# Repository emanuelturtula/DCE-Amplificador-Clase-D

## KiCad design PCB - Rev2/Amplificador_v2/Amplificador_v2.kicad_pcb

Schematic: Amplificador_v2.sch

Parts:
C1, C3, C4, C5, C10, C11, C17, C19, C26, C34: 100n; C_0805_2012Metric
C2, C9, C12, C13, C55, C62, C65, C72, C74: 10u; CP_Elec_4x5.3
C6, C25: 220n; C_0805_2012Metric
C7, C14, C15: 3.3n; C_0805_2012Metric
C8, C22, C45, C46, C48, C49, C52: 1u; C_0805_2012Metric
C16: 1u; CP_Radial_D5.0mm_P2.00mm
C18: 33p; C_0805_2012Metric
C20, C33, C64, C73: 10u; CP_Radial_D4.0mm_P1.50mm
C21, C43, C44: 100u; CP_Radial_D8.0mm_P3.50mm
C23, C24: 10u; C_0805_2012Metric
C27, C28: 1n; C_0805_2012Metric
C29, C30, C32: C; C_1206_3216Metric
C31: 330n; C_Rect_L18.0mm_W5.0mm_P15.00mm_FKS3_FKP3
C35, C36, C37, C38, C58, C59, C60, C61, C63, C66, C67, C68, C69, C70, C71: C; C_0805_2012Metric
C39, C40, C41, C42: 3300u; CP_Radial_D18.0mm_P7.50mm
C47, C50, C51: 100u; CP_Elec_6.3x7.7
C53, C54: 2200u; CP_Radial_D13.0mm_P5.00mm
C56, C57: 10u; CP_Radial_D5.0mm_P2.00mm
D1, D2: 1N4148W; D_SOD-123
D3, D4, D5: MURS120T3G; D_SMB_Handsoldering
D6, D7: MURS320T3G; D_SMC_Handsoldering
IC1, IC2: AD817; SOIC-8_3.9x4.9mm_P1.27mm; MPN AD817ARZ
J1, J2, J3, J7, J10: Conn_01x02_Male; PinHeader_1x02_P2.54mm_Vertical
J4, J5, J8: Conn_01x03_Male; PinHeader_1x03_P2.54mm_Vertical
J6, J12: Screw_Terminal_01x02; TerminalBlock_bornier-2_P5.08mm
J9, J11: Screw_Terminal_01x03; TerminalBlock_bornier-3_P5.08mm
JP1, JP2, JP3, JP4, JP7: Jumper; SolderJumper-2_P1.3mm_Open_RoundedPad1.0x1.5mm
JP5: Jumper_3_Open; PinHeader_1x03_P2.54mm_Vertical
JP6: Jumper_Preampli; SolderJumper-2_P1.3mm_Open_RoundedPad1.0x1.5mm
L1: INDUCTOR; 15333C
Q1, Q2, Q3, Q6, Q7, Q10, Q12, Q14: BC847; SOT-23
Q4, Q13: 2N7002; SOT-23
Q5, Q8, Q9, Q11, Q15: BC857; SOT-23
Q16, Q17: PHB27NQ10T; TO-263-2
R1, R2: 100k; R_0805_2012Metric
R3: 5.6k; R_0805_2012Metric
R4, R6, R11, R12: 100; R_0805_2012Metric
R5, R7, R15, R29, R31, R32, R35, R39, R40, R41, R42, R43, R44, R45, R46, R47, R48, R49, R50, R51, R52, R53, R54, R55, R56: R; R_0805_2012Metric
R8, R9, R10, R13, R16, R17, R28, R30, R33, R34: 1k; R_0805_2012Metric
R14: 3.9k; R_0805_2012Metric
R18: 2.7k; R_0805_2012Metric
R19: 49.9; R_0805_2012Metric
R20: 10; R_2512_6332Metric
R21, R23: 1.2; R_0805_2012Metric
R22, R24: 3.3; R_0805_2012Metric
R25, R26, R27, R37, R38: R; R_2512_6332Metric
R36: 18k; R_0805_2012Metric
RV1, RV2: 200; Potentiometer_Bourns_3296W_Vertical
RV3, RV4, RV5: R_POT; Potentiometer_Alps_RK163_Single_Horizontal
RV6: 10k; Potentiometer_Bourns_3296W_Vertical
TP1, TP2, TP3, TP4, TP5, TP6, TP7, TP8, TP9: TestPoint; TestPoint_Pad_1.0x1.0mm
TP10, TP11, TP12: TestPoint; TestPoint_Pad_2.0x2.0mm
U1: TL082; SOIC-8_3.9x4.9mm_P1.27mm
U2, U3, U5: LM311; SOIC-8_3.9x4.9mm_P1.27mm
U4: SN74LVC2G02DCUR; VSSOP-8_3.0x3.0mm_P0.65mm
U6: UCC20520DWR; SOIC127P1030X265-16N
U7: LM7812_TO220; TO-220-3_Vertical
U8: LM7815_TO220; TO-220-3_Vertical
U9: LM7915_TO220; TO-220-3_Vertical
U10: LM7805_TO220; TO-220-3_Vertical
U11, U12: NE5532; SOIC-8_3.9x4.9mm_P1.27mm

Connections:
+5V: C5.1, C6.1, C14.1, C16.1, C17.1, C51.1, C52.1, C55.1, C56.1, C57.1, J10.1, R8.1, R9.1, R16.1, U4.8 (VCC), U6.3 (VCCI-1), U6.8 (VCCI), U10.3 (VO)
+15V: C1.1, C2.1, C3.1, C4.1, C10.1, C12.1, C33.1, C34.1, C47.1, C49.1, C62.1, C63.1, C64.1, C67.1, C72.1, C73.1, IC1.7, IC2.7, J1.1, Q2.3 (C), Q14.3 (C), R1.1, R11.1, R12.1, U1.8 (V+), U2.8 (V+), U3.8 (V+), U5.8 (V+), U8.3 (VO), U10.1 (VI), U11.8 (V+), U12.8 (V+)
-15V: C11.2, C13.2, C33.2, C34.2, C48.2, C50.2, C64.2, C65.2, C66.1, C68.1, C73.2, C74.2, IC1.4, IC2.4, J2.1, U5.4 (V-), U9.3 (VO), U11.4 (V-), U12.4 (V-)
/Charge: D1.1 (K), R10.2, TP6.1, U4.6 (2B), U4.7 (1Y)
/Discharge: D2.1 (K), R13.2, TP7.1, U4.2 (1B), U4.3 (2Y)
/Filter_in: C70.1, JP5.2 (C), R52.1
/Filter_out: R54.2, R56.1, RV4.1
/HO: D4.2 (A), R22.1, U6.15 (OUTA)
/IN+: C60.2, J12.2
/IN-: C61.2, J12.1
/LEFT: C59.2, J11.1
/LO: D5.2 (A), R24.1, U6.10 (OUTB)
/RIGHT: C58.2, J11.3
/Reset: R9.2, TP5.1, U3.7, U4.5 (2A)
/Set: R8.2, TP4.1, U2.7, U4.1 (1A)
/U+: R7.2, TP2.1, U1.1, U2.3 (-)
/U-: Q3.3 (C), R5.1, TP3.1, U3.2 (+)
/VDDA: C19.1, C22.1, D3.2 (A), U6.16 (VDDA)
/VDDB: C20.1, C23.1, C25.1, R20.2, U6.11 (VDDB), U7.3 (VO)
/Vref: R5.2, R7.1, TP1.1, U1.2 (-)
/Vtriang_off: C7.1, Q11.3 (C), Q12.3 (C), TP8.1, U1.5 (+), U2.2 (+), U3.3 (-)
Error_amplifier_in: J4.3, R28.1
Error_amplifier_out: C38.1, J5.1, J7.1, R32.2, R35.2
GND: C1.2, C2.2, C3.2, C4.2, C5.2, C6.2, C7.2, C10.2, C11.1, C12.2, C13.1, C15.2, C16.2, C17.2, C18.2, C21.1, C24.1, C26.1, C31.2, C32.2, C35.1, C37.2, C39.2, C40.1, C41.2, C42.1, C43.2, C44.1, C45.2, C46.1, C47.2, C48.1, C49.2, C50.1, C51.2, C52.2, C54.2, C55.2, C56.2, C57.2, C62.2, C63.2, C65.1, C66.2, C67.2, C68.2, C71.2, C72.2, C74.1, J1.2, J2.2, J3.2, J9.2, J10.2, J11.2, JP3.1 (A), JP4.1 (A), JP7.1 (A), Q4.2 (S), Q8.3 (C), Q13.2 (S), Q15.3 (C), R2.2, R4.2, R6.2, R15.2, R17.2, R18.2, R29.2, R33.2, R38.1, R41.2, R42.2, R50.1, R53.2, R55.2, U1.4 (V-), U2.1 (GND), U2.4 (V-), U3.1 (GND), U3.4 (V-), U4.4 (GND), U5.1 (GND), U6.4 (GND), U7.1 (VI), U8.2 (GND), U9.1 (GND), U10.2 (GND), U12.5 (+)
unnamed: C8.1, C9.1, U1.6 (-), U1.7
unnamed: C8.2, C9.2, JP1.1 (A), TP9.1
unnamed: C14.2, JP3.2 (B), R17.1, U6.5 (DISABLE)
unnamed: C15.1, R18.1, U6.6 (DT)
unnamed: C18.1, R19.2, U6.1 (PWM)
unnamed: C27.1, Q16.1 (G), R21.2, R22.2, TP11.1
unnamed: C28.1, Q17.1 (G), R23.2, R24.2, TP12.1
unnamed: C29.1, R25.1
unnamed: C30.1, R26.1
unnamed: C32.1, R27.1
unnamed: C35.2, IC1.3, R28.2, R29.1
unnamed: C36.1, C38.2, IC1.6, J7.2, R31.2, R35.1
unnamed: C36.2, IC1.2, R30.2, R31.1
unnamed: C37.1, R32.1
unnamed: C53.2, C54.1, J6.2, JP4.2 (B), JP7.2 (B), R37.1, R38.2
unnamed: C58.1, R39.1
unnamed: C59.1, R40.1
unnamed: C60.1, R41.1, U11.3 (+)
unnamed: C61.1, R42.1, U11.5 (+)
unnamed: C69.1, R53.1, RV3.3
unnamed: C69.2, R52.2, R54.1, RV3.1, RV3.2
unnamed: C70.2, R56.2, RV5.2, RV5.3
unnamed: C71.1, RV5.1
unnamed: D1.2 (A), Q4.1 (G), R10.1
unnamed: D2.2 (A), Q13.1 (G), R13.1
unnamed: D3.1 (K), R20.1
unnamed: D4.1 (K), R21.1
unnamed: D5.1 (K), R23.1
unnamed: IC2.2, IC2.6, R30.1
unnamed: IC2.3, R33.1, R34.2
unnamed: J4.1, J5.3
unnamed: J5.2, U5.2 (+)
unnamed: J8.2, R36.1
unnamed: JP2.1 (A), R16.2, TP10.1, U5.7
unnamed: JP5.1 (A), R47.2, U12.7
unnamed: JP5.3 (B), R51.2, U12.1
unnamed: JP6.1 (A), R55.1, RV4.2, RV4.3
unnamed: Q1.1 (B), Q2.2 (E), Q3.1 (B), Q7.1 (B), Q10.1 (B), Q15.1 (B)
unnamed: Q1.2 (E), R4.1
unnamed: Q1.3 (C), Q2.1 (B), R3.1
unnamed: Q3.2 (E), R6.1
unnamed: Q4.3 (D), RV1.2, RV1.3
unnamed: Q5.2 (E), R11.2
unnamed: Q5.3 (C), Q6.3 (C), Q8.1 (B)
unnamed: Q6.2 (E), Q7.3 (C)
unnamed: Q7.2 (E), RV1.1
unnamed: Q9.2 (E), R12.2
unnamed: Q10.2 (E), RV2.1
unnamed: Q10.3 (C), Q12.2 (E)
unnamed: Q11.1 (B), Q14.2 (E), R14.1
unnamed: Q9.3 (C), Q11.2 (E)
unnamed: Q6.1 (B), Q12.1 (B), Q15.2 (E), R14.2
unnamed: Q13.3 (D), RV2.2, RV2.3
unnamed: Q5.1 (B), Q8.2 (E), Q9.1 (B), Q14.1 (B)
unnamed: R1.2, R2.1, U1.3 (+)
unnamed: R3.2, RV6.2, RV6.3
unnamed: R34.1, R36.2
unnamed: R39.2, R40.2, R44.1
unnamed: R43.1, R45.1, U11.2 (-)
unnamed: R43.2, R46.1, U11.6 (-)
unnamed: R44.2, R47.1, U12.6 (-)
unnamed: R45.2, R48.1, U11.1
unnamed: R46.2, R49.1, U11.7
unnamed: R48.2, R51.1, U12.2 (-)
unnamed: R49.2, R50.2, U12.3 (+)
PWM: JP2.2 (B), R19.1
Signal_in: J3.1, J4.2, JP6.2 (B)
VCC: C39.1, C41.1, C43.1, C45.1, C53.1, D6.2 (A), J9.1, Q16.2 (D), R25.2, R37.2, RV6.1, U8.1 (VI)
VEE: C20.2, C21.2, C23.2, C24.2, C25.2, C26.2, C28.2, C30.2, C40.2, C42.2, C44.2, C46.2, D7.1 (K), J9.3, Q17.3 (S), U6.9 (VSSB), U7.2 (GND), U9.2 (VI)
VOUT: C31.1, J6.1, J8.3, L1.2, R27.2
VS: C19.2, C22.2, C27.2, C29.2, D6.1 (K), D7.2 (A), J8.1, L1.1, Q16.3 (S), Q17.2 (D), R26.2, U6.14 (VSSA)
Vtriang: JP1.2 (B), R15.1, U5.3 (-)

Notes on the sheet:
Bypass LM311 (los 2)
Bypass TL082
Bypass
GENERADOR DE ONDA TRIANGULAR
GENERADOR DE PWM
Dead Time
Startup protection
Filtro PWM
BOOTSTRAP
ETAPA DE SALIDA
REALIMENTADOR
Red de adelanto-atraso opcional
Snubber
Bypass (cerca de reguladores)
Bypass (cerca de entrada)

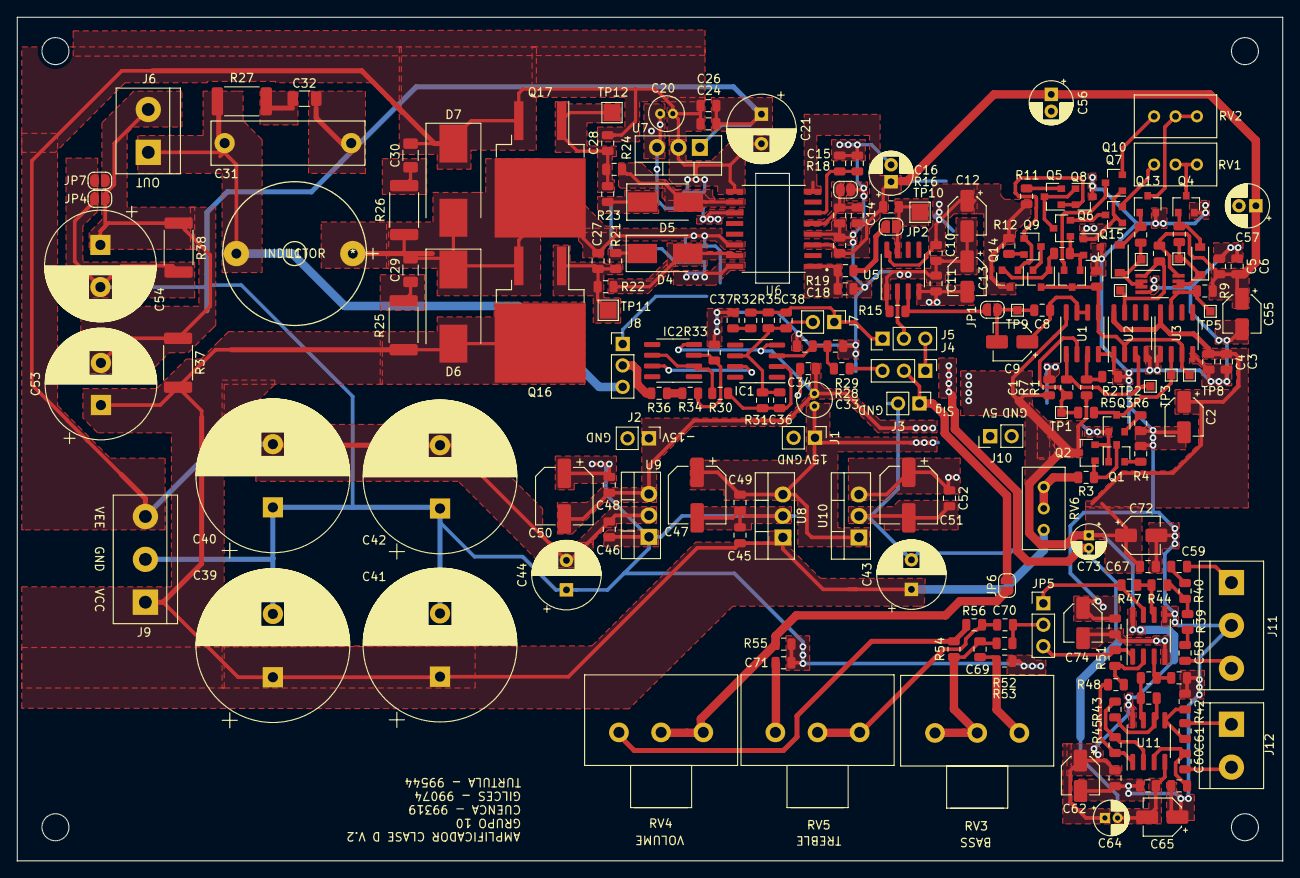
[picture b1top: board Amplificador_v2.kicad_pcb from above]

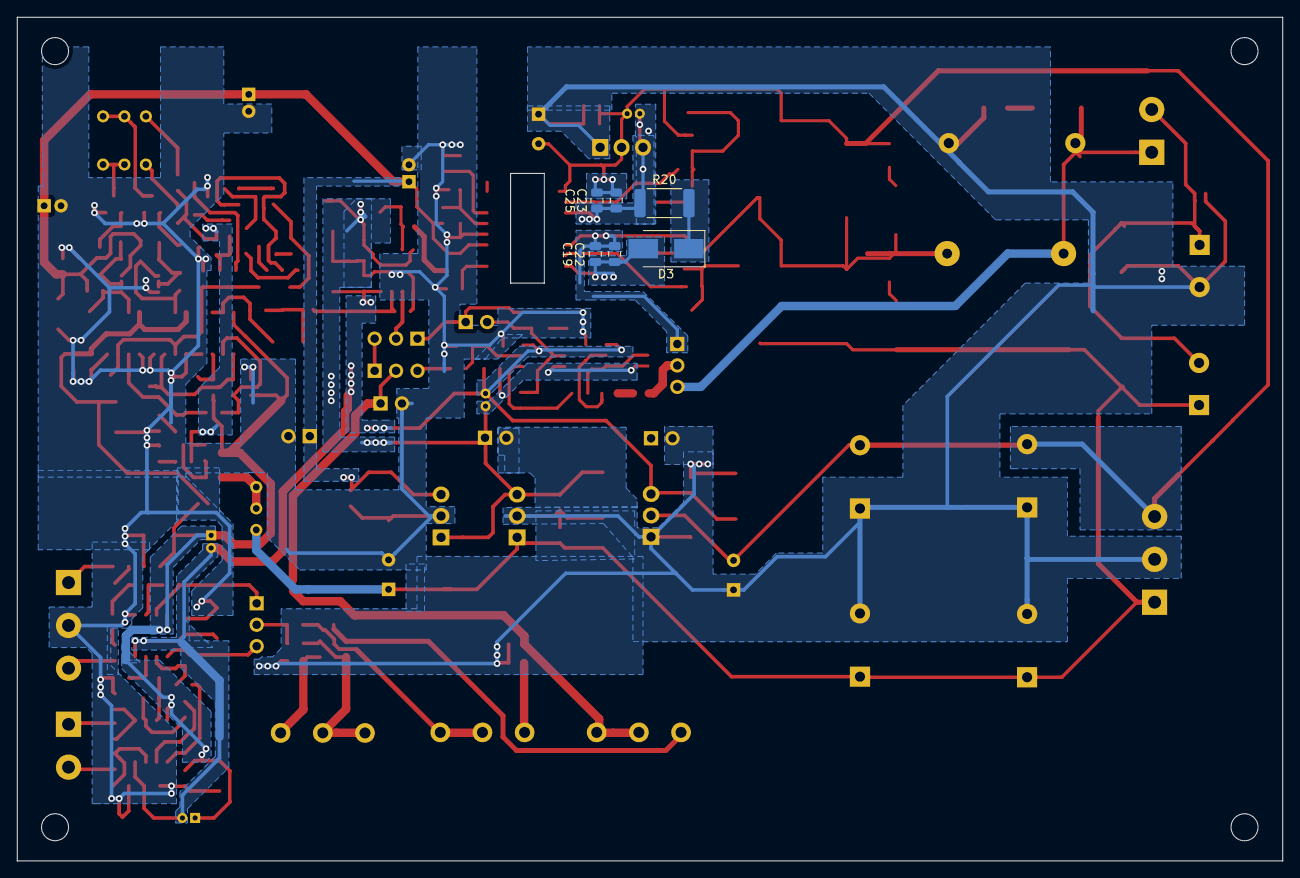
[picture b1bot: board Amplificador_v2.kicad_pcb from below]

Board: 2 copper layers, 150.0 x 100.0 mm, 206 parts (6 on the bottom side), 96 nets.

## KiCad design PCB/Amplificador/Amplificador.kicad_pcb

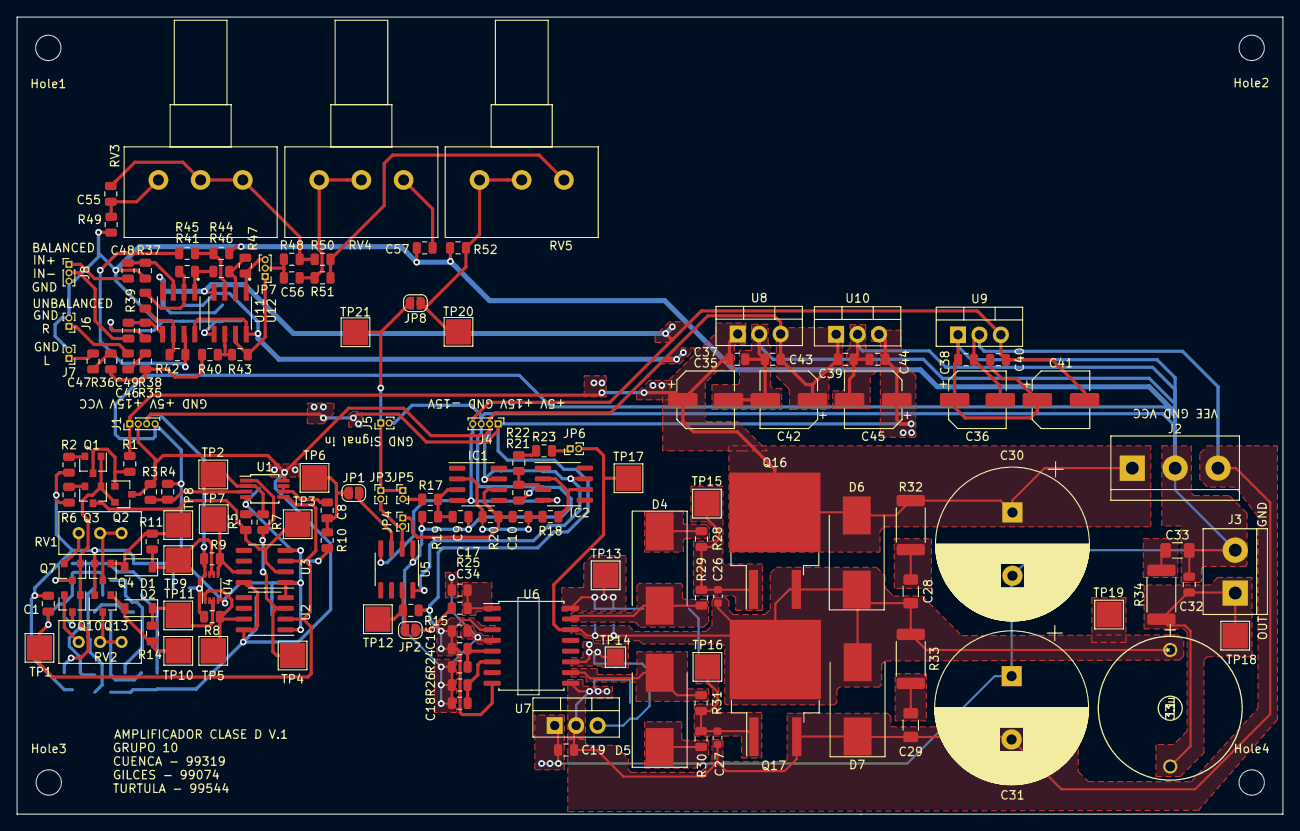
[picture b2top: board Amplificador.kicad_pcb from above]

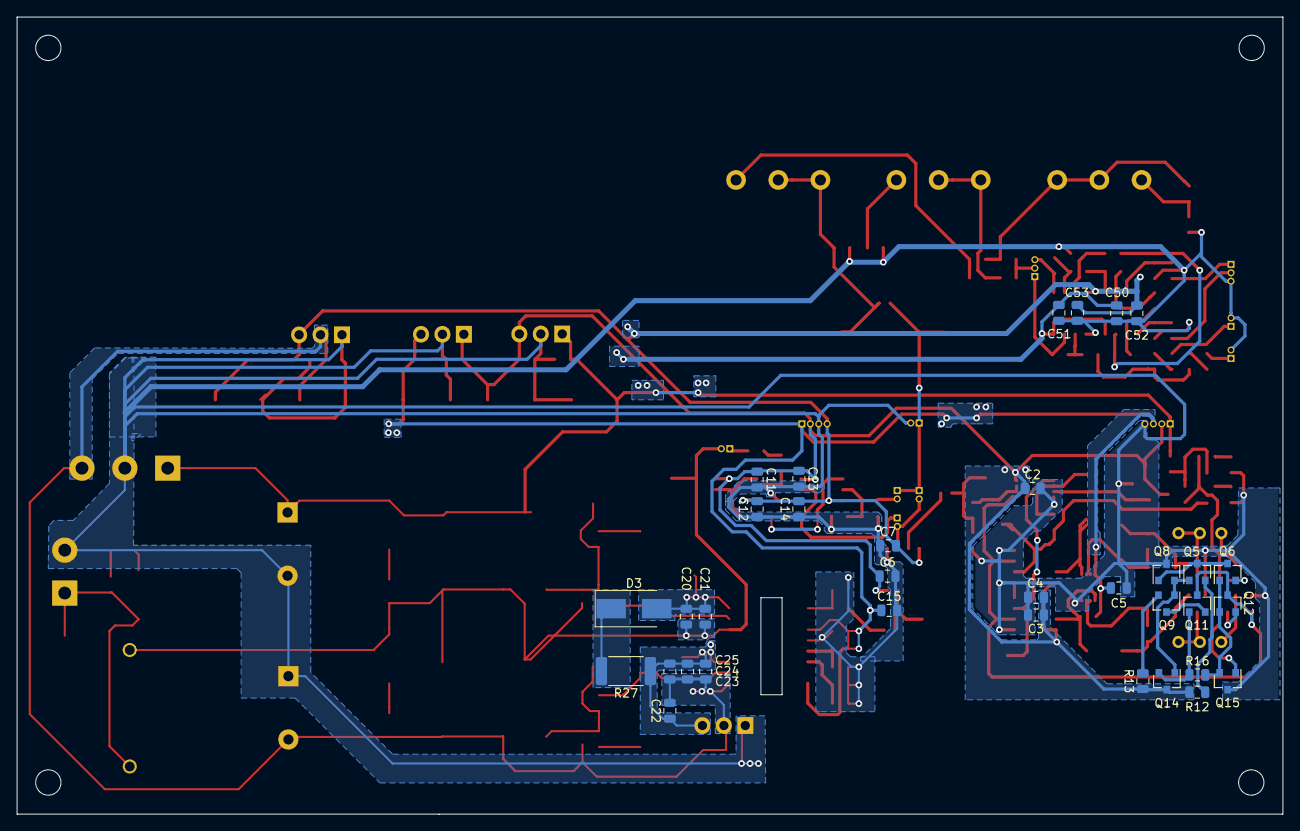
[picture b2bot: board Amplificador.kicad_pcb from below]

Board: 2 copper layers, 150.0 x 94.5 mm, 193 parts (34 on the bottom side), 91 nets.

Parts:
C1: 3.3n; C_0805_2012Metric
C2, C3, C4, C5, C6, C7, C11, C12, C13, C14, C15, C21, C22: 100n; C_0805_2012Metric
C8, C16, C34, C37, C38, C39, C40, C43, C44: 1u; C_0805_2012Metric
C9, C10: 220p; C_0805_2012Metric
C17: 33p; C_0805_2012Metric
C18: 2.2n; C_0805_2012Metric
C19, C23, C24: 10u; C_0805_2012Metric
C20, C25, C32: 330n; C_0805_2012Metric
C26, C27: 1n; C_0603_1608Metric
C28, C29, C33: C; C_1206_3216Metric
C30, C31: 3300u; CP_Radial_D18.0mm_P7.50mm
C35, C36: 33u; CP_Elec_6.3x7.7
C41, C42, C45: 47u; CP_Elec_6.3x5.4
C46, C47, C48, C49, C50, C51, C52, C53, C55, C56, C57: C; C_0805_2012Metric
D1, D2: 1N4148W; D_SOD-123
D3: MURS120T3G; D_SMB_Handsoldering
D4, D5, D6, D7: MURS320T3G; D_SMC_Handsoldering
Hole1, Hole2, Hole3, Hole4: MountingHole_3mm
IC1, IC2: AD817; SOIC-8_3.9x4.9mm_P1.27mm
J1, J4: Conector_Alimentacion; PinHeader_1x04_P1.00mm_Vertical
J2: Conector_Alimentacion; TerminalBlock_bornier-3_P5.08mm
J3: Salida; TerminalBlock_bornier-2_P5.08mm
J5: Entrada; PinHeader_1x02_P1.00mm_Vertical
J6, J7: Conn_01x02_Male; PinHeader_1x02_P1.00mm_Vertical
J8: Conn_01x03_Male; PinHeader_1x03_P1.00mm_Vertical
JP1: Jumper_Etapa_1; SolderJumper-2_P1.3mm_Open_RoundedPad1.0x1.5mm
JP2: Jumper_Etapa_2; SolderJumper-2_P1.3mm_Open_RoundedPad1.0x1.5mm
JP3, JP4, JP5, JP6: Jumper_NO_Small; PinHeader_1x02_P1.00mm_Vertical
JP7: Jumper_3_Open; PinHeader_1x03_P1.00mm_Vertical
JP8: Jumper_Preampli; SolderJumper-2_P1.3mm_Open_RoundedPad1.0x1.5mm
L1: 33u; 15333C
Q1, Q2, Q3, Q6, Q7, Q10, Q12, Q14: BC847; SOT-23
Q4, Q13: 2N7002; SOT-23
Q5, Q8, Q9, Q11, Q15: BC857; SOT-23
Q16, Q17: Q_NMOS_GDS; TO-263-2
R1: 10k; R_0805_2012Metric
R2, R6, R12, R13: 100; R_0805_2012Metric
R3, R4: 100k; R_0805_2012Metric
R5, R7: 330; R_0805_2012Metric
R8, R9, R11, R14, R15, R17, R18, R21, R22: 1k; R_0805_2012Metric
R10: 1.1k; R_0805_2012Metric
R16: 3.9k; R_0805_2012Metric
R19, R20: 82k; R_0805_2012Metric
R23: 18k; R_0805_2012Metric
R24: 1M; R_0805_2012Metric
R25: 49.9; R_0805_2012Metric
R26: 2.2k; R_0805_2012Metric
R27: 10; R_2512_6332Metric
R28, R30: 1.2; R_0805_2012Metric
R29, R31: 3.3; R_0805_2012Metric
R32, R33, R34: R; R_2512_6332Metric
R35, R36, R37, R38, R39, R40, R41, R42, R43, R44, R45, R46, R47, R48, R49, R50, R51, R52: R; R_0805_2012Metric
RV1, RV2: 200; Potentiometer_Bourns_3296W_Vertical
RV3, RV4, RV5: R_POT; Potentiometer_Alps_RK163_Single_Horizontal
TP1, TP2, TP3, TP4, TP5, TP6, TP7, TP8, TP9, TP10, TP11, TP12, TP13, TP15, TP16, TP17, TP18, TP19, TP20, TP21: TestPoint; TestPoint_Pad_3.0x3.0mm
TP14: TestPoint; TestPoint_Pad_2.0x2.0mm
U1: TL082; MSOP-8_3x3mm_P0.65mm
U2, U3, U5: LM311; SOIC-8_3.9x4.9mm_P1.27mm
U4: SN74LVC2G02DCUR; VSSOP-8_2.3x2mm_P0.5mm
U6: UCC20520DWR; SOIC-16W_7.5x10.3mm_P1.27mm
U7: LM7812_TO220; TO-220-3_Vertical
U8: LM7815_TO220; TO-220-3_Vertical
U9: LM7915_TO220; TO-220-3_Vertical
U10: LM7805_TO220; TO-220-3_Vertical
U11, U12: NE5532; SOIC127P599X175-8N

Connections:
+5V: C5.1, C15.1, C16.2, C34.1, C44.1, C45.1, J1.3, J4.1, R8.2, R9.2, R15.1, U4.8, U6.3, U6.8, U10.3
+15V: C2.1, C3.1, C4.1, C6.1, C11.1, C13.1, C39.1, C42.1, C43.1, C50.1, C51.1, IC1.7, IC2.7, J1.2, J4.2, Q2.3, Q14.3, R3.2, R12.1, R13.1, U1.8, U2.8, U3.8, U5.8, U8.3, U10.1, U11.8, U12.8
-15V: C7.2, C12.2, C14.2, C40.2, C41.2, C52.1, C53.1, IC1.4, IC2.4, J4.4, U5.4, U9.3, U11.4, U12.4
/EtapaSalida/DT: C18.1, R26.1, U6.6
/EtapaSalida/Disable: C16.1, R24.1, U6.5
/EtapaSalida/HO: D4.2, R29.2, U6.15
/EtapaSalida/LO: D5.2, R31.2, U6.10
/EtapaSalida/Out: C32.1, J3.1, L1.2, R34.1, TP18.1
/EtapaSalida/VDDA: C20.1, C21.1, D3.2, TP13.1, U6.16
/EtapaSalida/VDDB: C22.1, C23.1, C24.1, C25.1, R27.1, TP14.1, U6.11, U7.3
/GeneradorTriangular/Charge: D1.1, R11.1, TP9.1, U4.6, U4.7
/GeneradorTriangular/Discharge: D2.1, R14.1, TP11.1, U4.2, U4.3
/GeneradorTriangular/Reset: R9.1, TP7.1, U3.7, U4.5
/GeneradorTriangular/Set: R8.1, TP5.1, U2.7, U4.1
/GeneradorTriangular/U+: R7.2, TP4.1, U1.1, U2.3
/GeneradorTriangular/U-: Q3.3, R5.1, TP3.1, U3.2
/GeneradorTriangular/Vref: R5.2, R7.1, TP2.1, U1.2
/GeneradorTriangular/Vtriang_off: C1.1, Q11.3, Q12.3, TP1.1, U1.5, U2.2, U3.3
/Preamplificador/Filter_in: C56.1, JP7.2, R48.1
/Preamplificador/Filter_out: R50.2, R51.1, RV5.1
Feedback: C10.1, IC1.6, JP4.1, R20.1
GND: C1.2, C2.2, C3.2, C4.2, C5.2, C6.2, C7.1, C9.2, C11.2, C12.1, C13.2, C14.1, C15.2, C17.2, C18.2, C19.1, C30.2, C31.1, C32.2, C33.2, C34.2, C35.2, C36.1, C37.2, C38.1, C39.2, C40.1, C41.1, C42.2, C43.2, C44.2, C45.2, C50.2, C51.2, C52.2, C53.2, C57.2, J1.4, J2.2, J3.2, J4.3, J5.2, J6.2, J7.2, J8.3, Q4.2, Q8.3, Q13.2, Q15.3, R2.1, R4.1, R6.1, R10.2, R19.2, R21.2, R24.2, R26.2, R37.2, R38.2, R46.1, R49.2, R52.2, U1.4, U2.1, U2.4, U3.1, U3.4, U4.4, U5.1, U6.4, U7.1, U8.2, U9.1, U10.2, U12.5
In+: C48.2, J8.1
In-: C49.2, J8.2
Left: C47.2, J7.1
unnamed: C8.1, JP1.1, R10.1, TP6.1
unnamed: C8.2, U1.6, U1.7
unnamed: C9.1, IC1.3, R17.1, R19.1
unnamed: C10.2, IC1.2, R18.2, R20.2
unnamed: C17.1, R25.1, U6.1
unnamed: C26.1, Q16.1, R28.1, R29.1, TP15.1
unnamed: C27.1, Q17.1, R30.1, R31.1, TP16.1
unnamed: C28.1, R32.2
unnamed: C29.1, R33.2
unnamed: C33.1, R34.2
unnamed: C46.1, R35.1
unnamed: C47.1, R36.1
unnamed: C48.1, R37.1, U11.3
unnamed: C49.1, R38.1, U11.5
unnamed: C55.1, R49.1, RV3.3
unnamed: C55.2, R48.2, R50.1, RV3.1, RV3.2
unnamed: C56.2, R51.2, RV4.2, RV4.3
unnamed: C57.1, RV4.1
unnamed: D1.2, Q4.1, R11.2, TP8.1
unnamed: D2.2, Q13.1, R14.2, TP10.1
unnamed: D3.1, R27.2
unnamed: D4.1, R28.2
unnamed: D5.1, R30.2
unnamed: IC2.2, IC2.6, R18.1
unnamed: IC2.3, R21.1, R22.2
unnamed: JP2.1, R15.2, TP12.1, U5.7
unnamed: JP3.2, JP4.2, U5.2
unnamed: JP5.2, R17.2
unnamed: JP6.1, R23.1
unnamed: JP7.1, R43.2, U12.7
unnamed: JP7.3, R47.2, U12.1
unnamed: JP8.1, R52.1, RV5.2, RV5.3, TP20.1
unnamed: Q1.1, Q2.2, Q3.1, Q7.1, Q10.1, Q15.1
unnamed: Q1.2, R2.2
unnamed: Q1.3, Q2.1, R1.1
unnamed: Q3.2, R6.2
unnamed: Q4.3, RV1.2, RV1.3
unnamed: Q5.2, R12.2
unnamed: Q5.3, Q6.3, Q8.1
unnamed: Q6.2, Q7.3
unnamed: Q7.2, RV1.1
unnamed: Q9.2, R13.2
unnamed: Q10.2, RV2.1
unnamed: Q10.3, Q12.2
unnamed: Q11.1, Q14.2, R16.1
unnamed: Q9.3, Q11.2
unnamed: Q6.1, Q12.1, Q15.2, R16.2
unnamed: Q13.3, RV2.2, RV2.3
unnamed: Q5.1, Q8.2, Q9.1, Q14.1
unnamed: R3.1, R4.2, U1.3
unnamed: R22.1, R23.2
unnamed: R35.2, R36.2, R40.1
unnamed: R39.1, R41.1, U11.2
unnamed: R39.2, R42.1, U11.6
unnamed: R40.2, R43.1, U12.6
unnamed: R41.2, R44.1, U11.1
unnamed: R42.2, R45.1, U11.7
unnamed: R44.2, R47.1, U12.2
unnamed: R45.2, R46.2, U12.3
PWM: JP2.2, R25.2
Right: C46.2, J6.1
Signal_in: J5.1, JP3.1, JP5.1, JP8.2, TP21.1
VCC: C30.1, C35.1, C37.1, D6.2, J1.1, J2.1, Q16.2, R1.2, R32.1, U8.1
VEE: C19.2, C22.2, C23.2, C24.2, C25.2, C27.2, C29.2, C31.2, C36.2, C38.2, D7.1, J2.3, Q17.3, U6.9, U7.2, U9.2
Vs: C20.2, C21.2, C26.2, C28.2, D6.1, D7.2, JP6.2, L1.1, Q16.3, Q17.2, R33.1, TP17.1, TP19.1, U6.14
Vtriang: JP1.2, U5.3

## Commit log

2021-06-13 Ultima version de PCB y Esquematico
2021-06-13 Agregar mediciones de para snubber
2021-06-24 Agrego simulaciones y documentacion
2021-06-24 Generador de onda triangular terminado y ruteado
2021-06-27 Version sin preampli
2021-06-28 Finalizada la placa v2
2021-06-28 Placa finalizada y lista para enviar
2021-07-08 Last Version
2021-07-30 Terminado esto
2021-08-28 Aprobamos

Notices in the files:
parts and their libraries:
Copyright 2016 Accelerated Designs. All rights reserved.
